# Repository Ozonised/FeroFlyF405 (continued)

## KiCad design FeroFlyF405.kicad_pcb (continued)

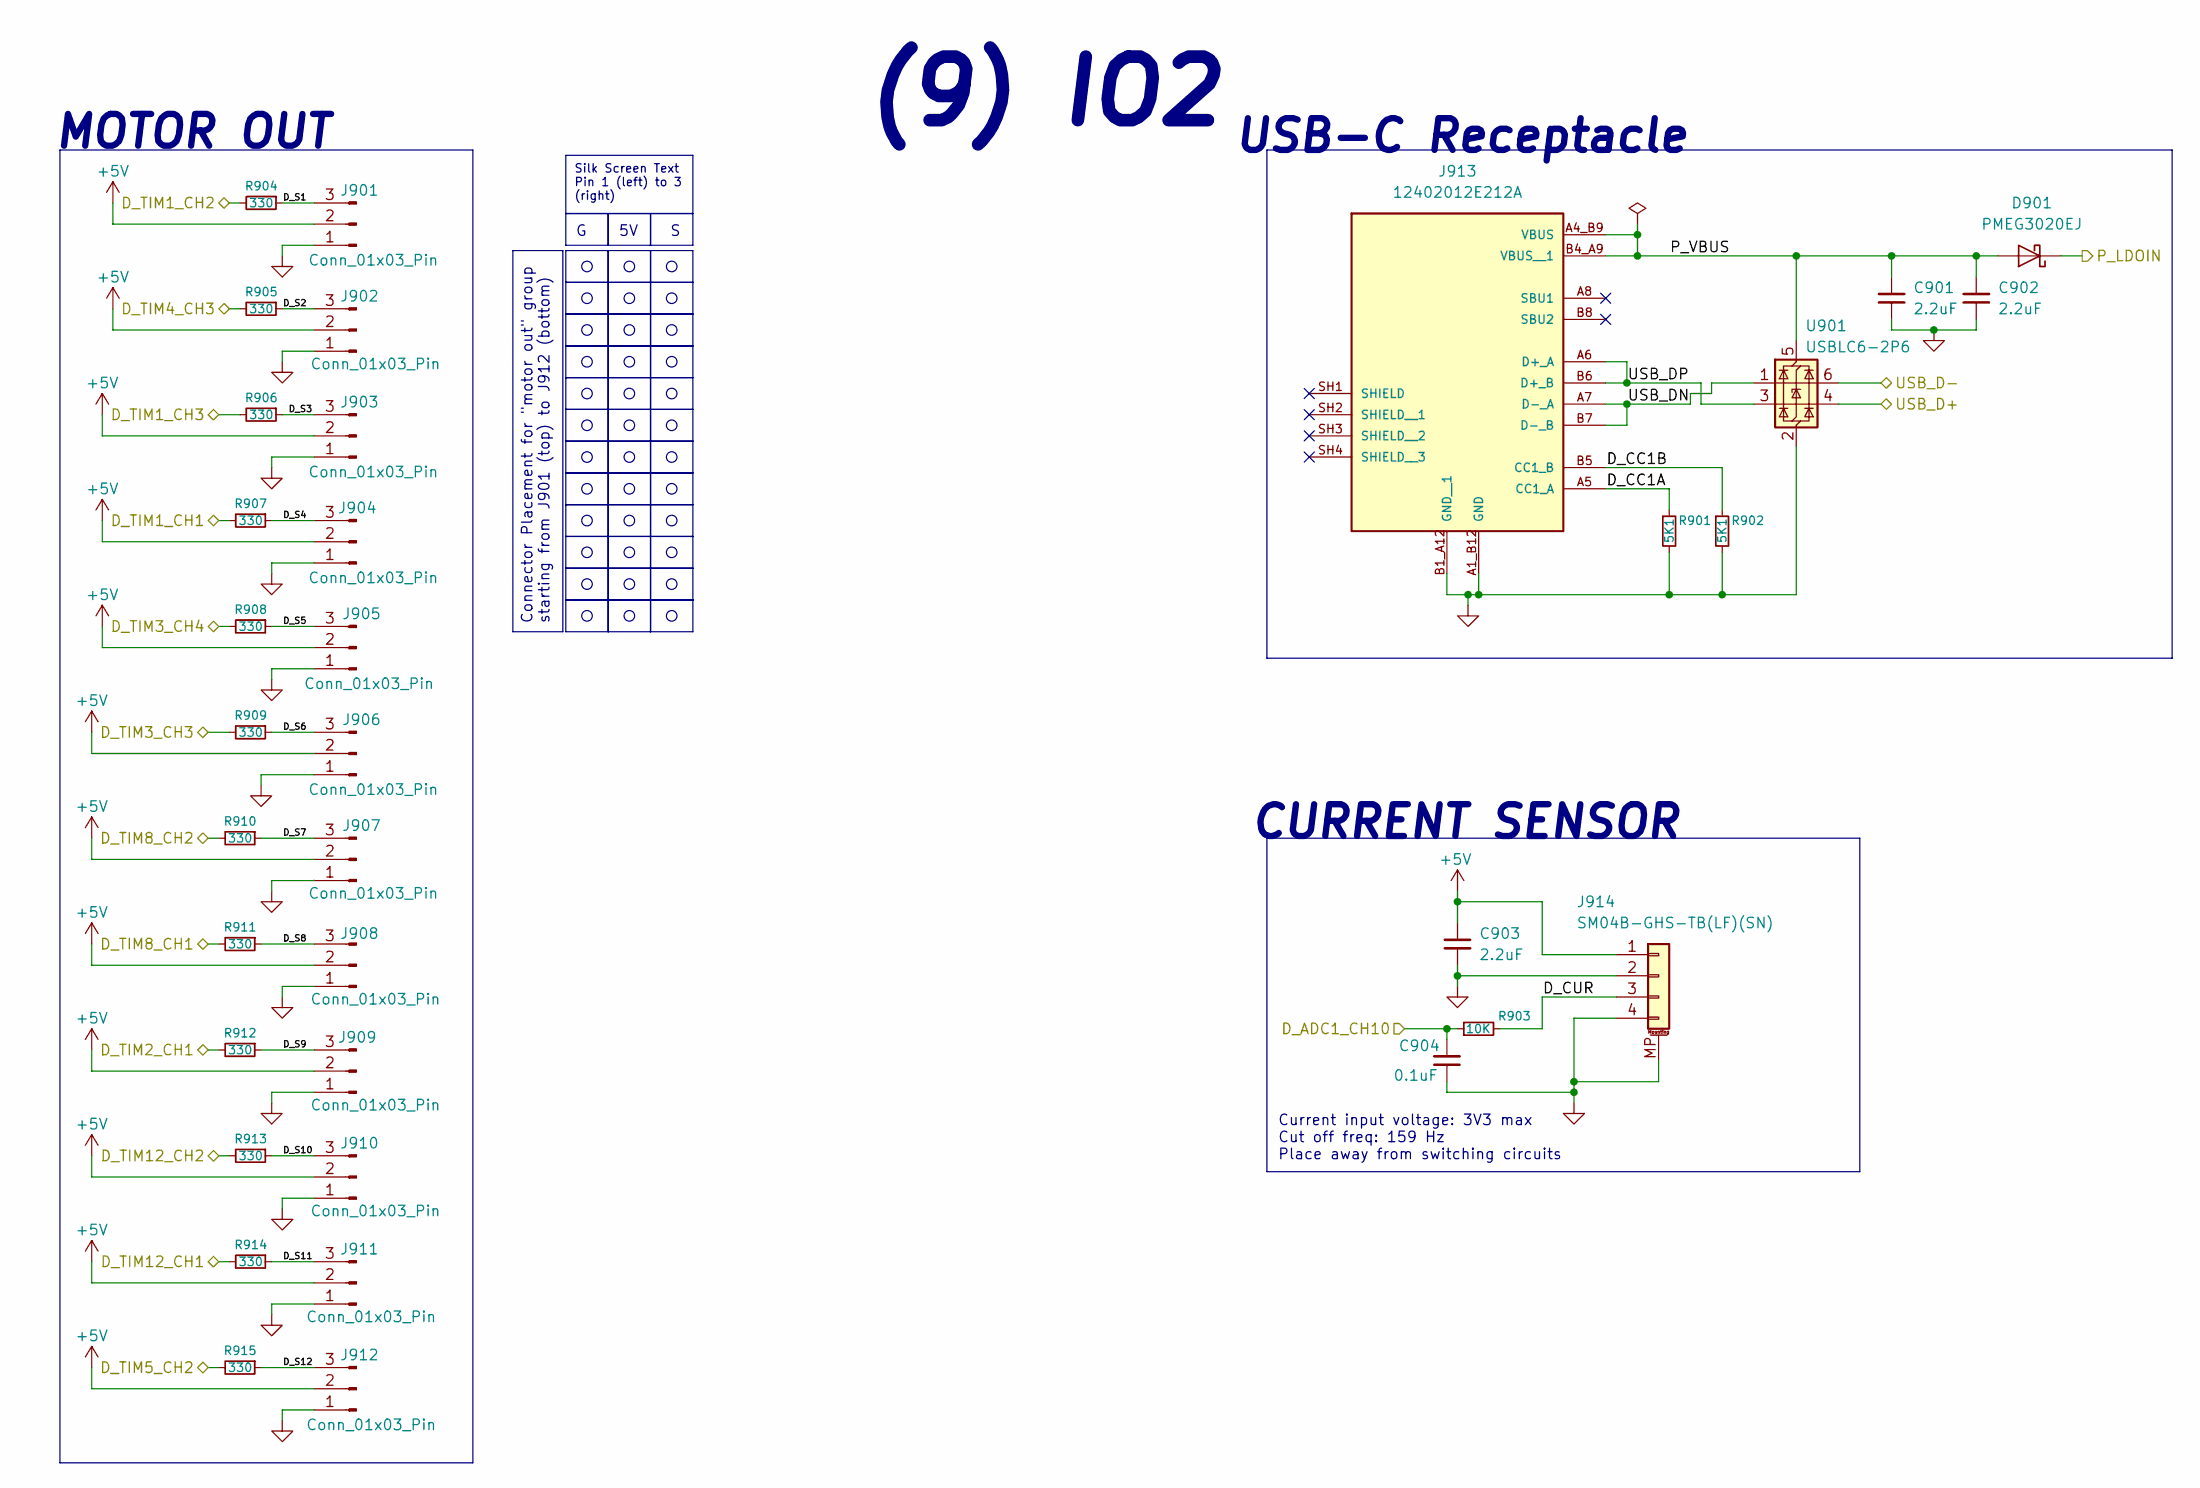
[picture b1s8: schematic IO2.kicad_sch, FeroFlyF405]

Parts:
C901, C902, C903: 2.2uF; C_0805_2012Metric_Pad1.18x1.45mm_HandSolder; MPN GCM21BR71C225KA64L
C904: 0.1uF; C_0603_1608Metric_Pad1.08x0.95mm_HandSolder; MPN C1608X5R1H104K080AA
D901: PMEG3020EJ; D_SOD-323F; MPN PMEG3020EJ,115
J901, J902, J903, J904, J905, J906, J907, J908, J909, J910, J911, J912: Conn_01x03_Pin; PinHeader_1x03_P2.54mm_Vertical
J913: 12402012E212A; AMPHENOL_12402012E212A; PARTREV 4
J914: SM04B-GHS-TB(LF)(SN); JST_GH_SM04B-GHS-TB_1x04-1MP_P1.25mm_Horizontal; MPN SM04B-GHS-TB(LF)(SN)
R901, R902: 5K1; R_0603_1608Metric_Pad0.98x0.95mm_HandSolder; MPN CR0603-FX-5101ELF
R903: 10K; R_0603_1608Metric_Pad0.98x0.95mm_HandSolder; MPN CR0603-FX-1002ELF
R904, R905, R906, R907, R908, R909, R910, R911, R912, R913, R914, R915: 330; R_0603_1608Metric_Pad0.98x0.95mm_HandSolder; MPN CR0603-FX-3300ELF
U901: USBLC6-2P6; SOT-666; MPN USBLC6-2P6

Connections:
+5V: C903.1, J901.2, J902.2, J903.2, J904.2, J905.2, J906.2, J907.2, J908.2, J909.2, J910.2, J911.2, J912.2, J914.1; also elsewhere on the board
/IO/D_ADC1_CH10: C904.1, R903.1; also elsewhere on the board
/IO/D_TIM1_CH1: R907.2; also elsewhere on the board
/IO/D_TIM1_CH2: R904.2; also elsewhere on the board
/IO/D_TIM1_CH3: R906.2; also elsewhere on the board
/IO/D_TIM2_CH1: R912.2; also elsewhere on the board
/IO/D_TIM3_CH3: R909.2; also elsewhere on the board
/IO/D_TIM3_CH4: R908.2; also elsewhere on the board
/IO/D_TIM4_CH3: R905.2; also elsewhere on the board
/IO/D_TIM5_CH2: R915.2; also elsewhere on the board
/IO/D_TIM8_CH1: R911.2; also elsewhere on the board
/IO/D_TIM8_CH2: R910.2; also elsewhere on the board
/IO/D_TIM12_CH1: R914.2; also elsewhere on the board
/IO/D_TIM12_CH2: R913.2; also elsewhere on the board
/IO/IO2/D_CC1A: J913.A5 (CC1_A), R901.1
/IO/IO2/D_CC1B: J913.B5 (CC1_B), R902.1
/IO/IO2/D_CUR: J914.3, R903.2
/IO/IO2/D_S1: J901.3, R904.1
/IO/IO2/D_S2: J902.3, R905.1
/IO/IO2/D_S3: J903.3, R906.1
/IO/IO2/D_S4: J904.3, R907.1
/IO/IO2/D_S5: J905.3, R908.1
/IO/IO2/D_S6: J906.3, R909.1
/IO/IO2/D_S7: J907.3, R910.1
/IO/IO2/D_S8: J908.3, R911.1
/IO/IO2/D_S9: J909.3, R912.1
/IO/IO2/D_S10: J910.3, R913.1
/IO/IO2/D_S11: J911.3, R914.1
/IO/IO2/D_S12: J912.3, R915.1
/IO/IO2/P_VBUS: C901.1, C902.1, D901.2 (A), J913.A4_B9 (VBUS), J913.B4_A9 (VBUS__1), U901.5 (VBUS)
/IO/IO2/USB_DN: J913.A7 (D-_A), J913.B7 (D-_B), U901.1 (I/O1)
/IO/IO2/USB_DP: J913.A6 (D+_A), J913.B6 (D+_B), U901.3 (I/O2)
/IO/P_LDOIN: D901.1 (K); also elsewhere on the board
/IO/USB_D+: U901.4 (I/O2); also elsewhere on the board
/IO/USB_D-: U901.6 (I/O1); also elsewhere on the board
GND: C901.2, C902.2, C903.2, C904.2, J901.1, J902.1, J903.1, J904.1, J905.1, J906.1, J907.1, J908.1, J909.1, J910.1, J911.1, J912.1, J913.A1_B12 (GND), J913.B1_A12 (GND__1), J914.2, J914.4, J914.MP (MountPin), R901.2, R902.2, U901.2 (GND); also elsewhere on the board

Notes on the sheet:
MOTOR OUT
G 5V S
USB-C Receptacle
Current input voltage: 3V3 max Cut off freq: 159 Hz Place away from switching circuits
(9) IO2
CURRENT SENSOR
Silk Screen Text Pin 1 (left) to 3 (right)
Connector Placement for "motor out" group starting from J901 (top) to J912 (bottom)

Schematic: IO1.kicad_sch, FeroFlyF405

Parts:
C801, C802, C803, C804, C805: 2.2uF; C_0805_2012Metric_Pad1.18x1.45mm_HandSolder; MPN GCM21BR71C225KA64L
J801, J805: SM06B-GHS-TB(LF)(SN); JST_GH_SM06B-GHS-TB_1x06-1MP_P1.25mm_Horizontal; MPN JST_GH_SM06B-GHS-TB
J802, J803, J804: SM04B-GHS-TB(LF)(SN); JST_GH_SM04B-GHS-TB_1x04-1MP_P1.25mm_Horizontal; MPN SM04B-GHS-TB(LF)(SN)
R801, R802: 330; R_0603_1608Metric_Pad0.98x0.95mm_HandSolder; MPN CR0603-FX-3300ELF
TP801, TP802, TP803, TP804, TP805, TP806, TP807: TestPoint; TestPoint_Pad_D1.0mm

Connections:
+5V: C801.1, C802.1, C803.1, C804.1, C805.1, J801.1, J802.1, J803.1, J804.1, J805.1; also elsewhere on the board
/IO/D_I2C1_SCL: J801.4, J803.2; also elsewhere on the board
/IO/D_I2C1_SDA: J801.5, J803.3; also elsewhere on the board
/IO/D_PINIO0: R801.2; also elsewhere on the board
/IO/D_PINIO1: R802.2; also elsewhere on the board
/IO/D_USART2_RX: J805.3, TP806.1 (1_1); also elsewhere on the board
/IO/D_USART2_TX: J805.2, TP805.1 (1_1); also elsewhere on the board
/IO/D_USART4_RX: J802.3; also elsewhere on the board
/IO/D_USART4_TX: J802.2; also elsewhere on the board
/IO/D_USART5_RX: J801.3; also elsewhere on the board
/IO/D_USART5_TX: J801.2; also elsewhere on the board
/IO/IO1/D_PINIO0R: J804.2, R801.1
/IO/IO1/D_PINIO1R: J804.3, R802.1
GND: C801.2, C802.2, C803.2, C804.2, C805.2, J801.6, J801.MP (MountPin), J802.4, J802.MP (MountPin), J803.4, J803.MP (MountPin), J804.4, J804.MP (MountPin), J805.6, J805.MP (MountPin), TP801.1 (1_1), TP802.1 (1_1), TP803.1 (1_1), TP804.1 (1_1), TP807.1 (1_1); also elsewhere on the board

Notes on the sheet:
Telemetry Port
I2C1 Port
PINIO
RC Receiver
(8) IO1
GPS Port
SILK SCREEN TEXT GUIDELINE

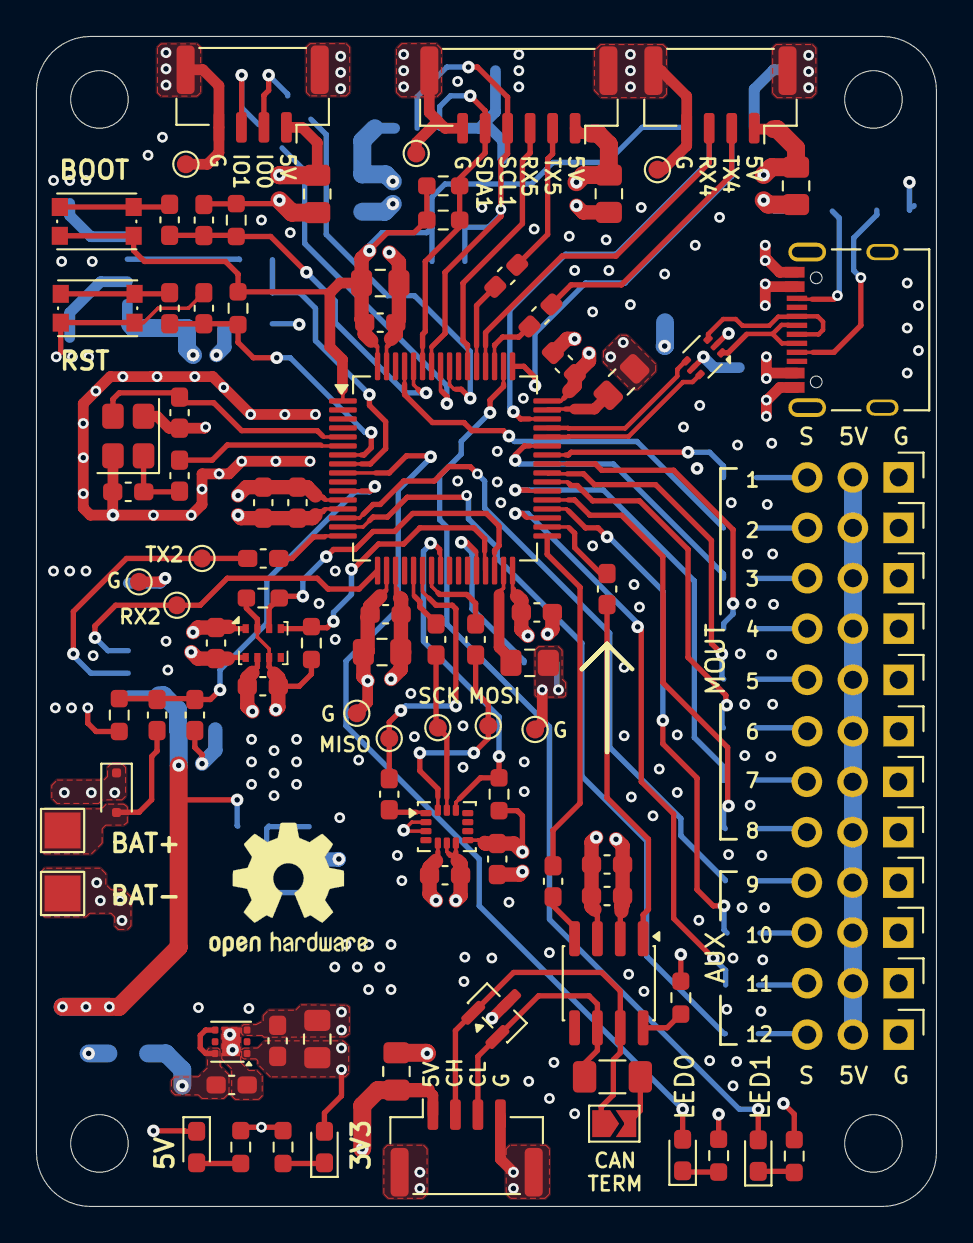
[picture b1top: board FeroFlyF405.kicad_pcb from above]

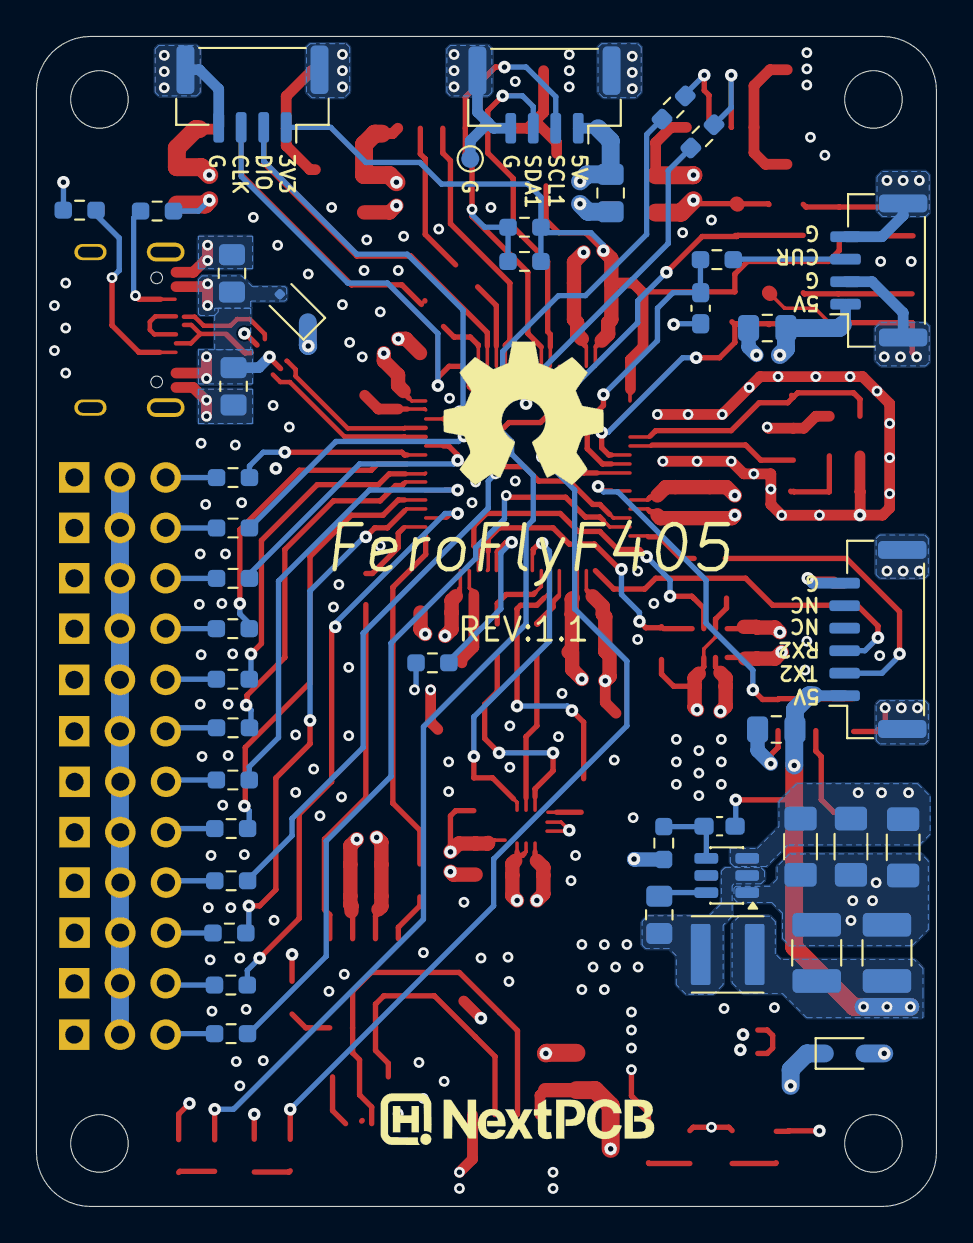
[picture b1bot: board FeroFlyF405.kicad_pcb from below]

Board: 4 copper layers, 50.0 x 65.0 mm, 147 parts (43 on the bottom side), 93 nets.
